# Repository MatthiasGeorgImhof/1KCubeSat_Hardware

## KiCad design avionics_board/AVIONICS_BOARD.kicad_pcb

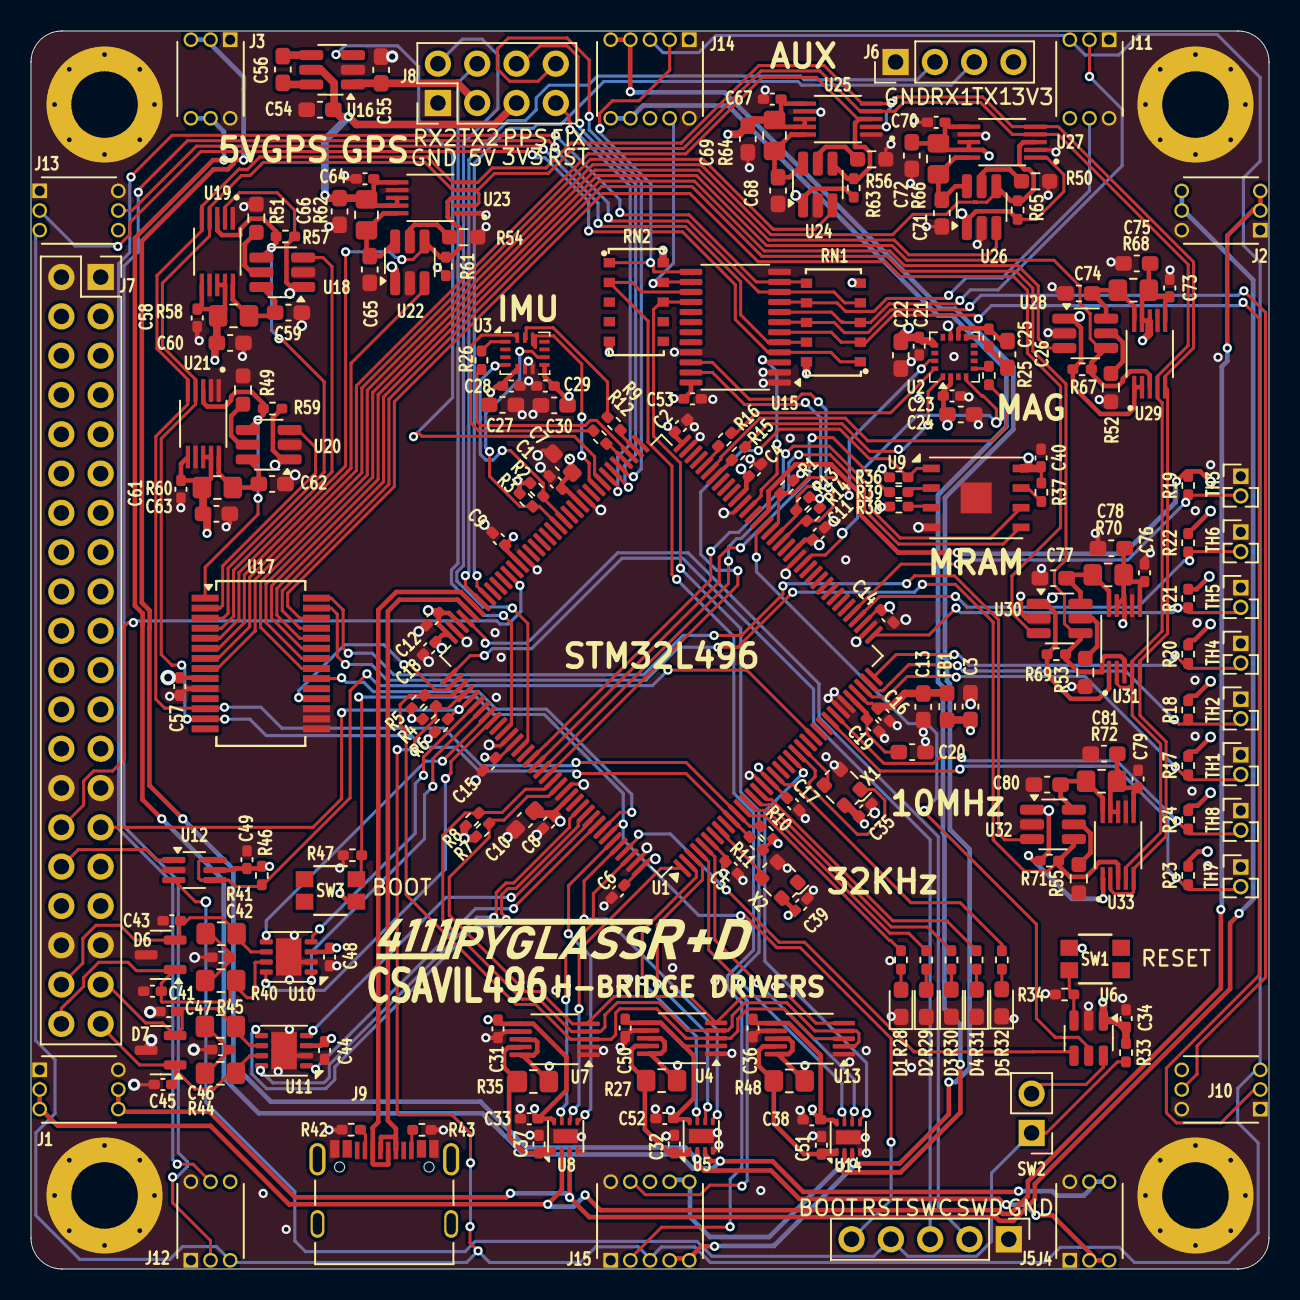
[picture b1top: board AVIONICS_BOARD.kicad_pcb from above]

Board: 4 copper layers, 80.0 x 80.0 mm, 228 parts (0 on the bottom side), 176 nets.

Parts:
C1, C2, C4, C5, C6, C8, C9, C11, C12, C14, C15, C16, C17, C18, C19, C21, C23, C25, C28, C29, C31, C32, C33, C34, C35, C36, C37, C38, C39, C40, C44, C48, C49, C50, C51, C52, C53, C57, C58, C61, C64, C67, C70, C73, C76, C79: 100nF; C_0402_1005Metric_Pad0.74x0.62mm_HandSolder
C3, C7, C10, C13, C20, C22, C24, C26, C27, C30, C54, C55: 10u; C_0603_1608Metric_Pad1.08x0.95mm_HandSolder
C41, C43, C45, C47: 100pF; C_0402_1005Metric_Pad0.74x0.62mm_HandSolder
C42, C46: 4.7nF; C_0402_1005Metric_Pad0.74x0.62mm_HandSolder
C56: 1uF; C_0603_1608Metric_Pad1.08x0.95mm_HandSolder
C59, C60, C62, C63, C65, C66, C68, C69, C71, C72, C74, C75, C77, C78, C80, C81: 10uF; C_0603_1608Metric_Pad1.08x0.95mm_HandSolder
D1: LED_SMD_RED; LED_0603_1608Metric_Pad1.05x0.95mm_HandSolder
D2: LED_SMD_GREEN; LED_0603_1608Metric_Pad1.05x0.95mm_HandSolder
D3, D4, D5: LED_SMD_YELLOW; LED_0603_1608Metric_Pad1.05x0.95mm_HandSolder
D6, D7: NUP2105LT1G; SOT-23
FB1: 120R; L_0603_1608Metric_Pad1.05x0.95mm_HandSolder
H1, H2, H3, H4: MountingHole_Pad; MountingHole_4.3mm_M4_Pad_Via_Custom
J1, J2, J3, J4, J10, J11, J12, J13: Conn_02x03_Odd_Even; HARWIN_M50-3200345
J5: Conn_01x06; PinHeader_1x05_P2.54mm_Vertical
J6: Conn_01x04; PinHeader_1x04_P2.54mm_Vertical
J7: PC104 Conn_02x20_Odd_Even; PinSocket_2x20_P2.54mm_Vertical
J8: Conn_02x04; PinHeader_2x04_P2.54mm_Vertical
J9: 10155435-00011LF; AMPHENOL_10155435-00011LF
J14, J15: Conn_02x05_Odd_Even; HARWIN_M50-3200545
R1, R2, R3, R4, R5, R33, R36, R37, R38, R46, R47, R57, R59, R61, R63, R65, R67, R69, R71: 100K; R_0402_1005Metric_Pad0.72x0.64mm_HandSolder
R6: 330K; R_0402_1005Metric_Pad0.72x0.64mm_HandSolder
R7, R8, R10, R11, R13, R14, R42, R43: 5K1; R_0402_1005Metric_Pad0.72x0.64mm_HandSolder
R9, R12, R15, R16, R25, R26: 22; R_0402_1005Metric_Pad0.72x0.64mm_HandSolder
R17, R18, R19, R20, R21, R22, R23, R24: 47K; R_0402_1005Metric_Pad0.72x0.64mm_HandSolder
R27, R35, R48, R58, R60, R62, R64, R66, R68, R70, R72: 10m; R_0805_2012Metric_Pad1.20x1.40mm_HandSolder
R28, R29, R30, R31, R32: 1K; R_0402_1005Metric_Pad0.72x0.64mm_HandSolder
R34: 8K87; R_0402_1005Metric_Pad0.72x0.64mm_HandSolder
R39: 22R; R_0402_1005Metric_Pad0.72x0.64mm_HandSolder
R40, R41, R44, R45: 60R4; R_0805_2012Metric_Pad1.20x1.40mm_HandSolder
R49, R50, R51, R52, R53, R54, R55, R56: 988R; R_0603_1608Metric_Pad0.98x0.95mm_HandSolder
RN1, RN2: 4K7; C_ARRAY_EXBA_PAN
SW1, SW3: EVP-AA602W; EVP602AA
SW2: SW_DIP_x01; PinHeader_1x02_P2.54mm_Vertical
TH1, TH2, TH3, TH4, TH5, TH6, TH7, TH8: Thermistor_NTC; PinHeader_1x02_P1.27mm_Vertical
U1: STM32L496ZGTx; LQFP-144_20x20mm_P0.5mm
U2: MMC5983MA; LGA-16_3x3mm_P0.5mm
U3: BMI270; Bosch_LGA-14_3x2.5mm_P0.5mm
U4, U7, U13: INA226; VSSOP-10_3x3mm_P0.5mm
U5, U8, U14: DRV8838; WSON-8-1EP_2x2mm_P0.5mm_EP0.9x1.6mm
U6: TPL5010; SOT-23-6
U9: MR25H10; DFN-8-1EP_6x5mm_P1.27mm_EP2x2mm
U10, U11: TCAN3414; VSON-8-1EP_3x3mm_P0.65mm_EP1.65x2.4mm
U12: 74LVC2G07; SOT-363_SC-70-6_Handsoldering
U15: TCA9548APWR; TSSOP-24_4.4x7.8mm_P0.65mm
U16: AP3602AKTR-G1; SOT-23-6_Handsoldering
U17: MCP23017T-E/SS; SSOP-28_5.3x10.2mm_P0.65mm
U18, U20, U22, U24, U26, U28, U30, U32: MIC2009A-1YM6-TR; SOT-23-6_Handsoldering
U19, U21, U23, U25, U27, U29, U31, U33: INA226AIDGSR; SOP50P490X110-10N
X1: 10MHz; Oscillator_SMD_ECS_2520MV-xxx-xx-4Pin_2.5x2.0mm
X2: 32.768KHZ; Oscillator_SMD_ECS_2520MV-xxx-xx-4Pin_2.5x2.0mm

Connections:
/3.3V_ACS_LOGIC: C31.1, C33.1, C36.1, C38.1, C50.1, C52.1, C61.1, C63.1, R60.2, U4.2 (A0), U4.6 (VS), U5.8 (VCC), U7.6 (VS), U8.8 (VCC), U13.6 (VS), U14.8 (VCC), U21.6 (VS), U21.8 (VBUS), U21.9 (IN-)
/3.3V_AUX: C57.1, J7.22, R57.1, R59.1, R61.1, R63.1, R65.1, R67.1, R69.1, R71.1, U17.9 (VDD), U18.1 (VIN), U19.2 (A0), U20.1 (VIN), U22.1 (VIN), U24.1 (VIN), U26.1 (VIN), U27.1 (A1), U28.1 (VIN), U29.1 (A1), U29.2 (A0), U30.1 (VIN), U31.1 (A1), U32.1 (VIN), U33.1 (A1)
/3.3V_CLK: C35.1, C76.1, C78.1, R70.2, U31.6 (VS), U31.8 (VBUS), U31.9 (IN-), X1.4 (VDD)
/3.3V_GPS: C54.1, C64.1, C66.1, J8.5, R62.2, U16.5 (VIN), U23.6 (VS), U23.8 (VBUS), U23.9 (IN-)
/3.3V_GYRO: C27.1, C28.1, C29.1, C30.1, C58.1, C60.1, R58.2, U3.5 (VDDIO), U3.8 (VDD), U19.6 (VS), U19.8 (VBUS), U19.9 (IN-)
/3.3V_MAG: C21.2, C22.1, C23.2, C24.1, C70.1, C72.1, R66.2, U2.2 (VDD), U2.13 (VDDIO), U27.6 (VS), U27.8 (VBUS), U27.9 (IN-)
/3.3V_MRAM: C40.1, C73.1, C75.1, R36.1, R37.1, R38.1, R68.2, U9.8 (VDD), U29.6 (VS), U29.8 (VBUS), U29.9 (IN-)
/3.3V_STM_CORE: C1.1, C2.1, C3.1, C4.1, C5.2, C6.1, C7.2, C8.2, C9.2, C10.2, C11.1, C12.2, C14.1, C15.2, C17.1, C18.2, C34.1, C39.1, C44.1, C48.1, C49.2, FB1.1, J6.4, J7.9, R1.1, R2.1, R3.1, R4.1, R5.1, R6.1, R7.1, R8.1, R10.1, R11.1, R13.1, R14.1, R33.1, R46.1, SW1.1, SW3.1, U1.6 (VBAT), U1.17 (VDD), U1.39 (VDD), U1.52 (VDD), U1.62 (VDD), U1.72 (VDD), U1.84 (VDD), U1.95 (VDDIO2), U1.106 (VDDUSB), U1.108 (VDD), U1.121 (VDD), U1.131 (VDDIO2), U1.144 (VDD), U6.1 (VDD), U10.3 (VCC), U11.3 (VCC), U12.5 (VCC), X2.4 (VCC)
/3.3V_SUN: C53.1, C67.1, C69.1, J10.6, J11.6, J12.6, J13.6, J14.6, J15.6, R64.2, RN1.5, RN1.10, RN2.5, RN2.10, U15.24 (VCC), U25.6 (VS), U25.8 (VBUS), U25.9 (IN-)
/5V_ACS_COIL: J7.5, R27.1, R35.1, R48.1, U4.8 (Vbus), U4.10 (Vin+), U7.8 (Vbus), U7.10 (Vin+), U13.8 (Vbus), U13.10 (Vin+)
/*ATTENTION: J7.29, R6.2, U1.113 (PC12)
/*AVI_RST: J7.32, U12.1 (IN1)
/*EPS_RST: J7.30, U1.97 (PC7)
/ACS/X_N: J1.4, J1.6, J2.4, J2.6, U8.3 (OUT2)
/ACS/X_P: J1.3, J1.5, J2.3, J2.5, U8.2 (OUT1)
/ACS/Y_N: J3.4, J3.6, J4.4, J4.6, U5.3 (OUT2)
/ACS/Y_P: J3.3, J3.5, J4.3, J4.5, U5.2 (OUT1)
/ACS_INT: R5.2, U1.111 (PC10), U4.3 (~Alert), U7.3 (~Alert), U13.3 (~Alert)
/ACS_X_PH: U1.1 (PE2), U8.6 (PH)
/ACS_X_SLEEP: U1.142 (PE1), U8.7 (~SLEEP)
/ACS_Y_PH: U1.3 (PE4), U5.6 (PH)
/ACS_Y_SLEEP: U1.2 (PE3), U5.7 (~SLEEP)
/ACS_Z_PH: U1.5 (PE6), U14.6 (PH)
/ACS_Z_SLEEP: U1.4 (PE5), U14.7 (~SLEEP)
/ADC1_IN3: R23.1, TH7.2, U1.28 (PC2)
/ADC1_IN4: R24.1, TH8.2, U1.29 (PC3)
/ADC1_IN5: R17.1, TH1.2, U1.34 (PA0)
/ADC1_IN6: R18.1, TH2.2, U1.35 (PA1)
/ADC1_IN7: R20.1, TH4.2, U1.36 (PA2)
/ADC1_IN8: R21.1, TH5.2, U1.37 (PA3)
/ADC1_IN9: R22.1, TH6.2, U1.40 (PA4)
/ADC1_IN10: R19.1, TH3.2, U1.41 (PA5)
/CAN1_H: C41.1, D6.1 (K), J7.40, R40.1, U10.7 (CANH)
/CAN1_L: C43.2, D6.2 (K), J7.38, R41.2, U10.6 (CANL)
/CAN2_H: C45.1, D7.1 (K), J7.39, R44.1, U11.7 (CANH)
/CAN2_L: C47.2, D7.2 (K), J7.37, R45.2, U11.6 (CANL)
/GPS_INTERFACE/CAN_POWER6/VOUT: C55.1, J8.3, U16.1 (VOUT)
/GPS_INTERFACE/FIX: J8.8, U1.77 (PD8)
/GPS_INTERFACE/PPS: J8.6, U1.78 (PD9)
/GPS_INTERFACE/SHDN_5V: U1.80 (PD11), U16.3 (*SHDN)
/GPS_RESET: J8.7, U1.79 (PD10)
/GYRO1_INT: R2.2, U1.87 (PG2), U3.4 (INT1)
/GYRO2_INT: R3.2, U1.88 (PG3), U3.9 (INT2)
/GYRO_CS: U1.81 (PD12), U3.12 (CSB)
/I2C1_SCL: R7.2, U1.129 (PG14), U4.5 (SCL), U7.5 (SCL), U13.5 (SCL)
/I2C1_SDA: R8.2, U1.128 (PG13), U4.4 (SDA), U7.4 (SDA), U13.2 (A0), U13.4 (SDA)
/I2C2_SCL: R10.2, U1.11 (PF1), U17.12 (SCL), U19.5 (SCL), U21.5 (SCL), U23.5 (SCL), U25.2 (A0), U25.5 (SCL), U27.5 (SCL), U29.5 (SCL), U31.5 (SCL), U33.2 (A0), U33.5 (SCL)
/I2C2_SDA: R11.2, U1.10 (PF0), U17.13 (SDA), U19.4 (SDA), U21.4 (SDA), U23.2 (A0), U23.4 (SDA), U25.4 (SDA), U27.4 (SDA), U29.4 (SDA), U31.2 (A0), U31.4 (SDA), U33.4 (SDA)
/I2C4_SCL: R14.2, U1.54 (PF14), U15.22 (SCL)
/I2C4_SDA: R13.2, U1.55 (PF15), U15.23 (SDA)
/MAG_CS: U1.50 (PF12), U2.4 (SPI_CS)
/MAG_INT: R1.2, U1.56 (PG0), U2.15 (INT)
/Power_INT_EXTI7: U1.137 (PB7), U17.20 (INTA)
/Power_RST: U1.110 (PA15), U17.18 (*RESET)
/RST_SUN: U1.60 (PE9), U15.3 (~RESET)
/SPI1_MISO: R25.1, U1.67 (PE14)
/SPI1_MOSI: R16.1, U2.16 (SDA/SPI_SDI)
/SPI1_SCK: R15.1, U2.1 (SCL/SPI_SCK)
/SPI2_MISO: R26.2, U1.75 (PB14)
/SPI2_MOSI: R12.2, U3.14 (SDx)
/SPI2_SCK: R9.2, U3.13 (SCx)
/STM32L4/10MHZ_OE: U1.22 (PF10), X1.1 (TRI-STATE)
/STM32L4/BOOT0: J5.5, R47.1, SW3.2, U1.138 (PH3)
/STM32L4/CAN1_RX: U1.114 (PD0), U10.4 (RXD)
/STM32L4/CAN1_SHDN: U1.116 (PD2), U10.5 (SHTD)
/STM32L4/CAN1_STB: U1.117 (PD3), U10.8 (STB)
/STM32L4/CAN1_TX: U1.115 (PD1), U10.1 (TXD)
/STM32L4/CAN2_RX: U1.135 (PB5), U11.4 (RXD)
/STM32L4/CAN2_SHDN: U1.134 (PB4), U11.5 (SHTD)
/STM32L4/CAN2_STB: U1.133 (PB3), U11.8 (STB)
/STM32L4/CAN2_TX: U1.136 (PB6), U11.1 (TXD)
/STM32L4/JTCK_SWCLK: J5.3, U1.109 (PA14)
/STM32L4/JTMS_SWDIO: J5.2, U1.105 (PA13)
/STM32L4/LED_1: R28.1, U1.12 (PF2)
/STM32L4/LED_2: R29.1, U1.13 (PF3)
/STM32L4/LED_3: R30.1, U1.14 (PF4)
/STM32L4/LED_4: R31.1, U1.15 (PF5)
/STM32L4/LED_5: R32.1, U1.18 (PF6)
/STM32L4/MRAM_CS: R36.2, U1.127 (PG12), U9.1 (~CS)
/STM32L4/NRST: R46.2, U1.25 (NRST), U12.4 (OUT2), U12.6 (OUT1)
/STM32L4/RCC_OSC32_IN: U1.8 (PC14), X2.3 (OUT)
/STM32L4/RCC_OSC_IN: U1.23 (PH0), X1.3 (OUTPUT)
/STM32L4/RST: J5.4, R33.2, SW2.1, U12.3 (IN2)
/STM32L4/SPI3_MISO: R39.2, U1.125 (PG10)
/STM32L4/SPI3_MOSI: U1.126 (PG11), U9.5 (SI)
/STM32L4/SPI3_SCK: U1.124 (PG9), U9.6 (SCK)
/STM32L4/USART1_RX: J6.2, U1.102 (PA10)
/STM32L4/USART1_TX: J6.3, U1.101 (PA9)
/STM32L4/USB/DN: J9.A7 (DN1_A), J9.B7 (DN2_B), U1.103 (PA11)
/STM32L4/USB/DP: J9.A6 (DP1_A), J9.B6 (DP2_B), U1.104 (PA12)
/STM32L4/WATCHDOG_DONE: U1.141 (PE0), U6.4 (DONE)
/STM32L4/WATCHDOG_WAKE: U1.57 (PG1), U6.5 (WAKE)
/SUN_INT: J10.5, J11.5, J12.5, J13.5, J14.5, J15.5, R4.2, U1.112 (PC11)
/Solar Sensors/SC0: J13.4, RN1.9, U15.5 (SC0)
/Solar Sensors/SC1: J10.4, RN1.8, U15.7 (SC1)
/Solar Sensors/SC2: J11.4, RN1.7, U15.9 (SC2)
/Solar Sensors/SC3: J12.4, RN1.6, U15.11 (SC3)
/Solar Sensors/SC4: J14.4, RN2.9, U15.14 (SC4)
/Solar Sensors/SC5: J15.4, RN2.8, U15.16 (SC5)
/Solar Sensors/SD0: J13.3, RN1.1, U15.4 (SD0)
/Solar Sensors/SD1: J10.3, RN1.2, U15.6 (SD1)
/Solar Sensors/SD2: J11.3, RN1.3, U15.8 (SD2)
/Solar Sensors/SD3: J12.3, RN1.4, U15.10 (SD3)
/Solar Sensors/SD4: J14.3, RN2.1, U15.13 (SD4)
/Solar Sensors/SD5: J15.3, RN2.2, U15.15 (SD5)
/TEMP_PWR: R17.2, R18.2, R19.2, R20.2, R21.2, R22.2, R23.2, R24.2, U1.58 (PE7)
/TIM15_CH1: U1.21 (PF9), U14.5 (EN)
/TIM16_CH1: U1.139 (PB8), U8.5 (EN)
/TIM17_CH1: U1.140 (PB9), U5.5 (EN)
/USART2_RX: J8.2, U1.122 (PD6)
/USART2_TX: J8.4, U1.119 (PD5)
/Untitled Sheet/ENABLE0: U17.2 (GPB1), U20.3 (ENABLE)
/Untitled Sheet/ENABLE1: U17.4 (GPB3), U18.3 (ENABLE)
/Untitled Sheet/ENABLE2: U17.6 (GPB5), U22.3 (ENABLE)
/Untitled Sheet/ENABLE3: U17.8 (GPB7), U24.3 (ENABLE)
/Untitled Sheet/ENABLE4: U17.22 (GPA1), U26.3 (ENABLE)
/Untitled Sheet/ENABLE5: U17.24 (GPA3), U28.3 (ENABLE)
/Untitled Sheet/ENABLE6: U17.26 (GPA5), U30.3 (ENABLE)
/Untitled Sheet/ENABLE7: U17.28 (GPA7), U32.3 (ENABLE)
/Untitled Sheet/INT0: R59.2, U17.1 (GPB0), U20.4 (*FAULT), U21.3 (ALERT)
/Untitled Sheet/INT1: R57.2, U17.3 (GPB2), U18.4 (*FAULT), U19.3 (ALERT)
/Untitled Sheet/INT2: R61.2, U17.5 (GPB4), U22.4 (*FAULT), U23.3 (ALERT)
/Untitled Sheet/INT3: R63.2, U17.7 (GPB6), U24.4 (*FAULT), U25.3 (ALERT)
/Untitled Sheet/INT4: R65.2, U17.21 (GPA0), U26.4 (*FAULT), U27.3 (ALERT)
/Untitled Sheet/INT5: R67.2, U17.23 (GPA2), U28.4 (*FAULT), U29.3 (ALERT)
/Untitled Sheet/INT6: R69.2, U17.25 (GPA4), U30.4 (*FAULT), U31.3 (ALERT)
/Untitled Sheet/INT7: R71.2, U17.27 (GPA6), U32.4 (*FAULT), U33.3 (ALERT)
/Untitled Sheet/VOUT7: C79.1, C81.1, R72.2, U33.6 (VS), U33.8 (VBUS), U33.9 (IN-)
/Untitled Sheet/sheet601A160D5/ILIMIT+: R53.1, U30.5 (ILIMIT)
/Untitled Sheet/sheet601A160D6/ILIMIT+: R55.1, U32.5 (ILIMIT)
/Untitled Sheet/sheet601A160D7/ILIMIT+: R56.1, U24.5 (ILIMIT)
/Untitled Sheet/sheet601A160D8/ILIMIT+: R54.1, U22.5 (ILIMIT)
/Untitled Sheet/sheet601A160D9/ILIMIT+: R51.1, U18.5 (ILIMIT)
/Untitled Sheet/sheet601A160D10/ILIMIT+: R49.1, U20.5 (ILIMIT)
/Untitled Sheet/sheet601A160D11/ILIMIT+: R50.1, U26.5 (ILIMIT)
/Untitled Sheet/sheet601A160D12/ILIMIT+: R52.1, U28.5 (ILIMIT)
GND: C1.2, C2.2, C3.2, C4.2, C5.1, C6.2, C7.1, C8.1, C9.1, C10.1, C11.2, C12.1, C13.2, C14.2, C15.1, C16.2, C17.2, C18.1, C19.1, C20.1, C21.1, C22.2, C23.1, C24.2, C27.2, C28.2, C29.2, C30.2, C31.2, C32.2, C33.2, C34.2, C35.2, C36.2, C37.2, C38.2, C39.2, C40.2, C41.2, C42.2, C43.1, C44.2, C45.2, C46.2, C47.1, C48.2, C49.1, C50.2, C51.2, C52.2, C53.2, C54.2, C55.2, C57.2, C58.2, C59.2, C60.2, C61.2, C62.2, C63.2, C64.2, C65.2, C66.2, C67.2, C68.2, C69.2, C70.2, C71.2, C72.2, C73.2, C74.2, C75.2, C76.2, C77.2, C78.2, C79.2, C80.2, C81.2, D1.1 (K), D2.1 (K), D3.1 (K), D4.1 (K), D5.1 (K), D6.3 (A), D7.3 (A), H1.1, H2.1, H3.1, H4.1, J1.1, J1.2, J2.1, J2.2, J3.1, J3.2, J4.1, J4.2, J5.1, J6.1, J7.1, J7.2, J7.27, J7.28, J7.35, J7.36, J8.1, J9.A1_B12 (GND), J9.B1_A12 (GND__1), J10.1, J10.2, J11.1, J11.2, J12.1, J12.2, J13.1, J13.2, J14.1, J14.2, J15.1, J15.2, R34.2, R42.1, R43.1, R47.2, R49.2, R50.2, R51.2, R52.2, R53.2, R54.2, R55.2, R56.2, TH1.1, TH2.1, TH3.1, TH4.1, TH5.1, TH6.1, TH7.1, TH8.1, U1.16 (VSS), U1.30 (VSSA), U1.31 (VREF-), U1.38 (VSS), U1.51 (VSS), U1.61 (VSS), U1.71 (VSS), U1.83 (VSS), U1.94 (VSS), U1.107 (VSS), U1.120 (VSS), U1.130 (VSS), U1.143 (VSS), U2.11 (VSS), U3.6 (GNDIO), U3.7 (GND), U4.1 (A1), U4.7 (GND), U5.4 (GND), U5.9 (GND), U6.2 (GND), U7.1 (A1), U7.2 (A0), U7.7 (GND), U8.4 (GND), U8.9 (GND), U9.4 (VSS), U9.9 (PAD), U10.2 (GND), U10.9 (GND), U11.2 (GND), U11.9 (GND), U12.2 (GND), U13.1 (A1), U13.7 (GND), U14.4 (GND), U14.9 (GND), U15.1 (A0), U15.2 (A1), U15.12 (GND), U15.21 (A2), U16.2 (GND), U17.10 (VSS), U17.15 (A0), U17.16 (A1), U17.17 (A2), U18.2 (GND), U19.1 (A1), U19.7 (GND), U20.2 (GND), U21.1 (A1), U21.2 (A0), U21.7 (GND), U22.2 (GND), U23.1 (A1), U23.7 (GND), U24.2 (GND), U25.1 (A1), U25.7 (GND), U26.2 (GND), U27.2 (A0), U27.7 (GND), U28.2 (GND), U29.7 (GND), U30.2 (GND), U31.7 (GND), U32.2 (GND), U33.7 (GND), X1.2 (GND), X2.2 (GND)
unnamed: C25.1, C26.1, U2.9 (VSS)
unnamed: C42.1, R40.2, R41.1
unnamed: C46.1, R44.2, R45.1
unnamed: D1.2 (A), R28.2
unnamed: D2.2 (A), R29.2
unnamed: D3.2 (A), R30.2
unnamed: D4.2 (A), R31.2
unnamed: D5.2 (A), R32.2
unnamed: J9.A5 (CC1_A), R42.2
unnamed: J9.B5 (CC2_B), R43.2
unnamed: R9.1, U1.74 (PB13)
unnamed: R12.1, U1.76 (PB15)
unnamed: R15.2, U1.66 (PE13)
unnamed: R16.2, U1.68 (PE15)
unnamed: C13.1, C16.1, FB1.2, U1.33 (VDDA)
unnamed: C19.2, C20.2, U1.32 (VREF+)
unnamed: C25.2, C26.2, U2.10 (CAP)
unnamed: R25.2, U2.5 (SPI_SDO)
unnamed: R26.1, U3.1 (SDO)
unnamed: C32.1, R27.2, U4.9 (Vin-), U5.1 (VM)
unnamed: R34.1, SW1.2, U6.3 (DELAY/M_RST)
unnamed: SW2.2, U6.6 (~RST)
unnamed: C37.1, R35.2, U7.9 (Vin-), U8.1 (VM)
unnamed: R39.1, U9.2 (SO)
unnamed: R37.2, U9.7 (~HOLD)
unnamed: R38.2, U9.3 (~WP)
unnamed: C51.1, R48.2, U13.9 (Vin-), U14.1 (VM)
unnamed: C56.2, U16.6 (C+)
unnamed: C56.1, U16.4 (C-)
unnamed: C59.1, R58.1, U18.6 (VOUT), U19.10 (IN+)
unnamed: C62.1, R60.1, U20.6 (VOUT), U21.10 (IN+)
unnamed: C65.1, R62.1, U22.6 (VOUT), U23.10 (IN+)
unnamed: C68.1, R64.1, U24.6 (VOUT), U25.10 (IN+)
unnamed: C71.1, R66.1, U26.6 (VOUT), U27.10 (IN+)
unnamed: C74.1, R68.1, U28.6 (VOUT), U29.10 (IN+)
unnamed: C77.1, R70.1, U30.6 (VOUT), U31.10 (IN+)
unnamed: C80.1, R72.1, U32.6 (VOUT), U33.10 (IN+)
Z_N: J14.7, J14.9, J15.7, J15.9, U14.3 (OUT2)
Z_P: J14.8, J14.10, J15.8, J15.10, U14.2 (OUT1)

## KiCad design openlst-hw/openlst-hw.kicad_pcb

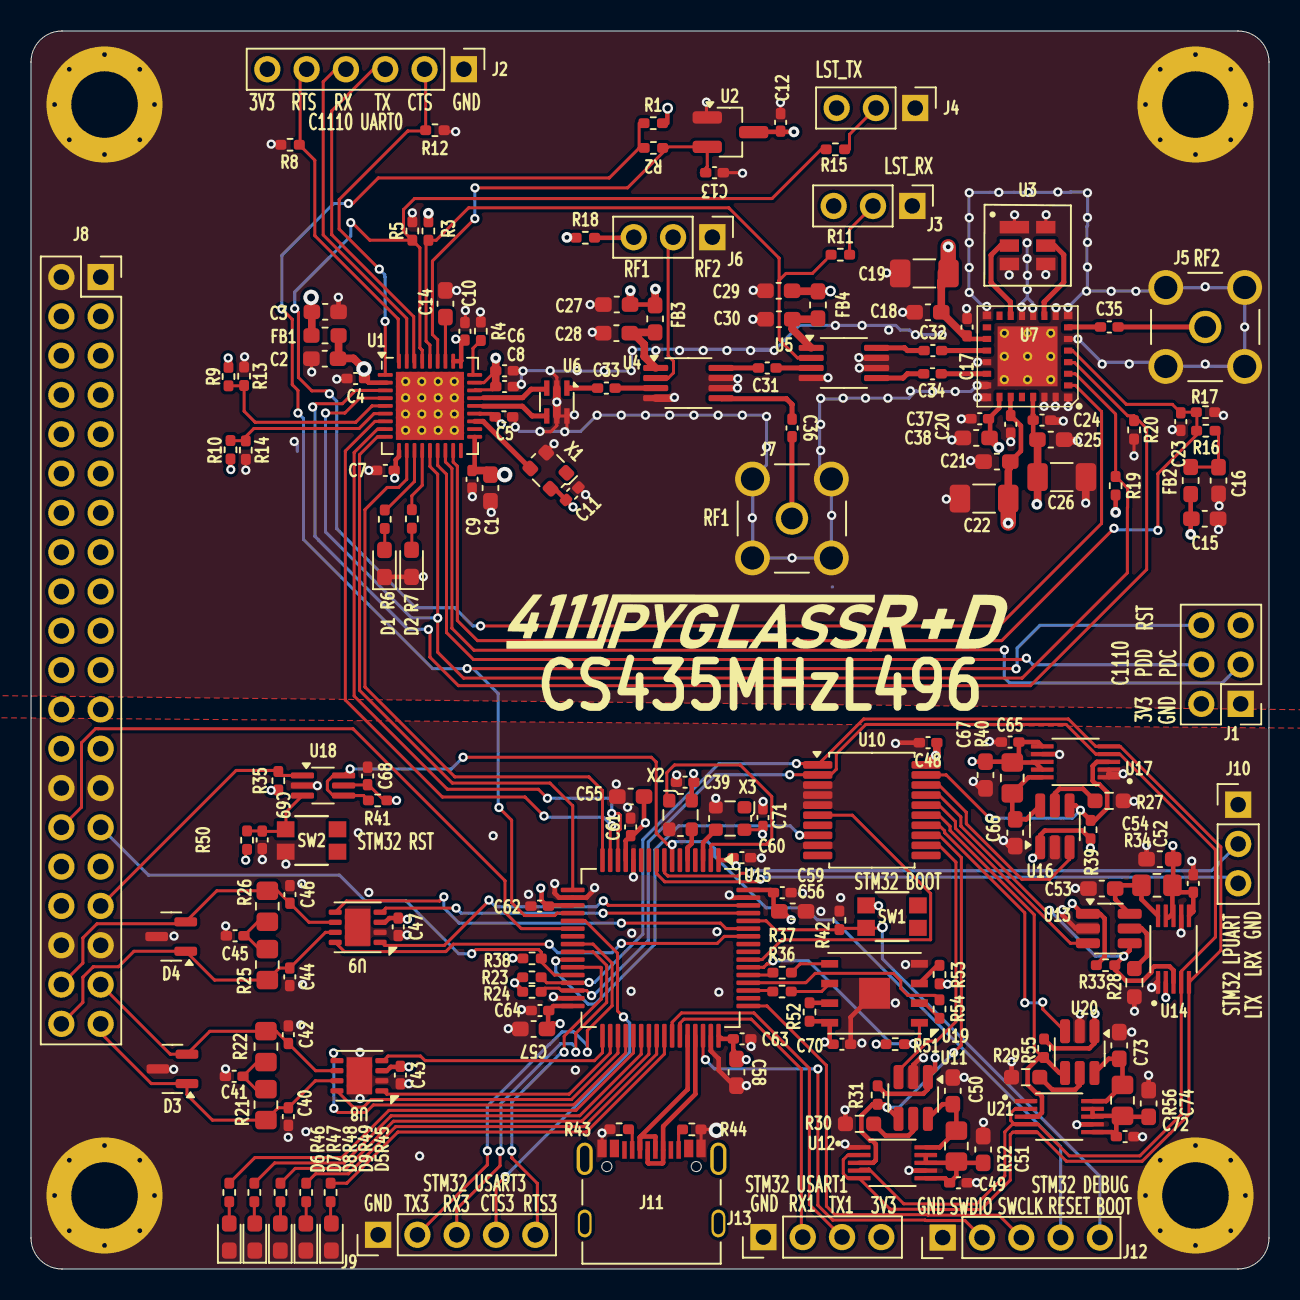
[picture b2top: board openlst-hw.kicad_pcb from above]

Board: 4 copper layers, 80.0 x 80.0 mm, 186 parts (0 on the bottom side), 134 nets.

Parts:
C1, C18, C21, C25, C38, C50, C51, C53, C54, C55, C56, C57, C58, C66, C67, C73, C74: 10uF; C_0603_1608Metric_Pad1.08x0.95mm_HandSolder
C2, C3, C14, C15, C16, C27, C28, C29, C30: 1uF; C_0603_1608Metric_Pad1.08x0.95mm_HandSolder
C4, C5, C6, C7, C8, C9, C10, C11, C12, C13, C17, C20, C23, C24, C37, C39, C43, C47, C48, C49, C52, C59, C60, C61, C62, C63, C64, C65, C68, C69, C70, C71, C72: 100nF; C_0402_1005Metric_Pad0.74x0.62mm_HandSolder
C19, C22, C26: 47uF; C_1206_3216Metric_Pad1.33x1.80mm_HandSolder
C31, C32, C33, C34, C35, C36: 220pF; C_0402_1005Metric_Pad0.74x0.62mm_HandSolder
C40, C42, C44, C46: 100pF; C_0402_1005Metric_Pad0.74x0.62mm_HandSolder
C41, C45: 4.7nF; C_0402_1005Metric_Pad0.74x0.62mm_HandSolder
D1, D2: ORANGE; LED_0603_1608Metric_Pad1.05x0.95mm_HandSolder
D3, D4: NUP2105LT1G; SOT-23
D5: LED_SMD_RED; LED_0603_1608Metric_Pad1.05x0.95mm_HandSolder
D6: LED_SMD_GREEN; LED_0603_1608Metric_Pad1.05x0.95mm_HandSolder
D7, D8, D9: LED_SMD_YELLOW; LED_0603_1608Metric_Pad1.05x0.95mm_HandSolder
FB1, FB2, FB3, FB4: 1K; L_0603_1608Metric_Pad1.05x0.95mm_HandSolder
H1, H2, H3, H4: MountingHole_Pad; MountingHole_4.3mm_M4_Pad_Via_Custom
J1: Conn_02x03_Pin; PinHeader_2x03_P2.54mm_Vertical
J2: Conn_01x06_Pin; PinHeader_1x06_P2.54mm_Vertical
J3, J4, J6, J10: Conn_01x03_Pin; PinHeader_1x03_P2.54mm_Vertical
J5, J7: SMA Jack; LINX_CONSMA001-G
J8: PC104 Conn_02x20_Odd_Even; PinSocket_2x20_P2.54mm_Vertical
J9: Conn_01x05_Pin; PinHeader_1x05_P2.54mm_Vertical
J11: 10155435-00011LF; AMPHENOL_10155435-00011LF
J12: Conn_01x06; PinHeader_1x05_P2.54mm_Vertical
J13: Conn_01x04; PinHeader_1x04_P2.54mm_Vertical
R1, R13, R14: 47K; R_0402_1005Metric_Pad0.72x0.64mm_HandSolder
R2, R6, R7, R19, R20, R45, R46, R47, R48, R49: 1K; R_0402_1005Metric_Pad0.72x0.64mm_HandSolder
R3, R5: 10K; R_0402_1005Metric_Pad0.72x0.64mm_HandSolder
R4: 56K; R_0402_1005Metric_Pad0.72x0.64mm_HandSolder
R8, R12, R31, R33, R35, R39, R41, R42, R50, R51, R52, R53, R55: 100K; R_0402_1005Metric_Pad0.72x0.64mm_HandSolder
R9, R10, R18: 20K; R_0402_1005Metric_Pad0.72x0.64mm_HandSolder
R11, R15: 22; R_0402_1005Metric_Pad0.72x0.64mm_HandSolder
R16: 3.09K; R_0402_1005Metric_Pad0.72x0.64mm_HandSolder
R17: 6.65K; R_0402_1005Metric_Pad0.72x0.64mm_HandSolder
R21, R22, R25, R26: 60R4; R_0805_2012Metric_Pad1.20x1.40mm_HandSolder
R23, R24, R43, R44: 5K1; R_0402_1005Metric_Pad0.72x0.64mm_HandSolder
R27, R28, R29, R30: 988R; R_0603_1608Metric_Pad0.98x0.95mm_HandSolder
R32, R34, R40, R56: 10m; R_0805_2012Metric_Pad1.20x1.40mm_HandSolder
R36, R37, R54: 22R; R_0402_1005Metric_Pad0.72x0.64mm_HandSolder
R38: 300K; R_0402_1005Metric_Pad0.72x0.64mm_HandSolder
SW1, SW2: EVP-AA602W; EVP602AA
U1: CC1110; Texas_RHH0036C_VQFN-36-1EP_6x6mm_P0.5mm_EP4.4x4.4mm_Thermal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
U2: MIC803; SOT-23_Handsoldering
U3: SF2446E
U4, U5: PE4250MLI; MSOP-8_3x3mm_P0.65mm
U6: 0433BM15A0001; Balun_Johanson_0896BM15A0001
U7: RFFM6406
U8, U9: TCAN3414; VSON-8-1EP_3x3mm_P0.65mm_EP1.65x2.4mm
U10: MCP23008T-E/SS; SSOP-20_5.3x7.2mm_P0.65mm
U11, U13, U16, U20: MIC2009A-1YM6-TR; SOT-23-6_Handsoldering
U12, U14, U17, U21: INA226AIDGSR; SOP50P490X110-10N
U15: STM32L496RGTx; LQFP-64_10x10mm_P0.5mm
U18: 74LVC2G07; SOT-363_SC-70-6_Handsoldering
U19: MR25H10; DFN-8-1EP_6x5mm_P1.27mm_EP2x2mm
X1: 27MHz; Oscillator_SMD_ECS_2520MV-xxx-xx-4Pin_2.5x2.0mm
X2: 10MHz; Oscillator_SMD_ECS_2520MV-xxx-xx-4Pin_2.5x2.0mm
X3: 32.768KHZ; Oscillator_SMD_ECS_2520MV-xxx-xx-4Pin_2.5x2.0mm

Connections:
/3V3_COMM: C3.1, C11.1, C12.2, C15.1, C27.1, C29.1, C37.1, C38.1, C65.1, C67.1, FB1.1, FB2.2, FB3.2, FB4.2, J1.2, J2.6, J3.3, J4.3, R1.2, R3.2, R9.2, R18.1, R19.2, R40.2, U2.3 (VCC), U7.23 (VDD), U17.6 (VS), U17.8 (VBUS), U17.9 (IN-), X1.4 (Vcc)
/CAN Bridge/3V3_MRAM: C52.1, C54.1, C70.1, R34.2, R51.1, R52.1, R53.1, U14.6 (VS), U14.8 (VBUS), U14.9 (IN-), U19.8 (VDD)
/CAN Bridge/ATTENTION: J8.29, R38.2, U15.28 (PB2)
/CAN Bridge/CAN1_H: C44.1, D4.1 (K), J8.40, R25.1, U9.7 (CANH)
/CAN Bridge/CAN1_L: C46.2, D4.2 (K), J8.38, R26.2, U9.6 (CANL)
/CAN Bridge/CAN2_H: C40.1, D3.1 (K), J8.39, R21.1, U8.7 (CANH)
/CAN Bridge/CAN2_L: C42.2, D3.2 (K), J8.37, R22.2, U8.6 (CANL)
/CAN Bridge/CAN Transceiver1/CAN_RX: U9.4 (RXD), U15.61 (PB8)
/CAN Bridge/CAN Transceiver1/CAN_TX: U9.1 (TXD), U15.62 (PB9)
/CAN Bridge/CAN Transceiver1/SHDN: U9.5 (SHTD), U15.59 (PB7)
/CAN Bridge/CAN Transceiver1/STB: U9.8 (STB), U15.58 (PB6)
/CAN Bridge/CAN Transceiver2/CAN_RX: U8.4 (RXD), U15.33 (PB12)
/CAN Bridge/CAN Transceiver2/CAN_TX: U8.1 (TXD), U15.34 (PB13)
/CAN Bridge/CAN Transceiver2/SHDN: U8.5 (SHTD), U15.36 (PB15)
/CAN Bridge/CAN Transceiver2/STB: U8.8 (STB), U15.35 (PB14)
/CAN Bridge/EPS_RST: J8.30, U15.22 (PA6)
/CAN Bridge/I2C2_SCL: R23.2, U10.1 (SCL), U12.2 (A0), U12.5 (SCL), U14.5 (SCL), U15.29 (PB10), U17.5 (SCL), U21.5 (SCL)
/CAN Bridge/I2C2_SDA: R24.2, U10.2 (SDA), U12.4 (SDA), U14.4 (SDA), U15.30 (PB11), U17.4 (SDA), U21.2 (A0), U21.4 (SDA)
/CAN Bridge/MRAM/SPI_CLK: R36.1, U19.6 (SCK)
/CAN Bridge/MRAM/SPI_CS: R51.2, U15.54 (PD2), U19.1 (~CS)
/CAN Bridge/MRAM/SPI_MISO: R54.2, U15.52 (PC11)
/CAN Bridge/MRAM/SPI_MOSI: R37.1, U19.5 (SI)
/CAN Bridge/PMIC/BOOT: J12.5, R42.1, SW1.2, U15.60 (PH3_BOOT0)
/CAN Bridge/PMIC/EXTR_RST: J8.33, R35.2, U18.1 (IN1)
/CAN Bridge/PMIC/HSE_EN: U15.2 (PC13), X2.1 (TRI-STATE)
/CAN Bridge/PMIC/HSE_IN: U15.5 (PH0), X2.3 (OUTPUT)
/CAN Bridge/PMIC/LED1: R45.1, U15.37 (PC6)
/CAN Bridge/PMIC/LED2: R46.1, U15.38 (PC7)
/CAN Bridge/PMIC/LED3: R47.1, U15.39 (PC8)
/CAN Bridge/PMIC/LED4: R48.1, U15.40 (PC9)
/CAN Bridge/PMIC/LED5: R49.1, U15.41 (PA8)
/CAN Bridge/PMIC/LPUART_RX: J10.2, U15.8 (PC0)
/CAN Bridge/PMIC/LPUART_TX: J10.3, U15.9 (PC1)
/CAN Bridge/PMIC/OSC32_IN: U15.3 (PC14), X3.3 (OUT)
/CAN Bridge/PMIC/RESET: J12.4, R41.2, U15.7 (NRST), U18.4 (OUT2), U18.6 (OUT1)
/CAN Bridge/PMIC/RESET/RESET: C69.1, R50.2, SW2.3, U18.3 (IN2)
/CAN Bridge/PMIC/SYS_JTMS_SWCLK: J12.3, U15.49 (PA14)
/CAN Bridge/PMIC/SYS_JTMS_SWDIO: J12.2, U15.46 (PA13)
/CAN Bridge/PMIC/USART1_RX: J13.2, U15.43 (PA10)
/CAN Bridge/PMIC/USART1_TX: J13.3, U15.42 (PA9)
/CAN Bridge/PMIC/USART3_CTS: J9.4, U15.21 (PA5)
/CAN Bridge/PMIC/USART3_RTS: J9.5, U15.27 (PB1)
/CAN Bridge/PMIC/USART3_RX: J9.3, U15.25 (PC5)
/CAN Bridge/PMIC/USART3_TX: J9.2, U15.24 (PC4)
/CAN Bridge/PMIC/USB/DN: J11.A7 (DN1_A), J11.B7 (DN2_B), U15.44 (PA11)
/CAN Bridge/PMIC/USB/DP: J11.A6 (DP1_A), J11.B6 (DP2_B), U15.45 (PA12)
/CAN Bridge/Power Switch/ENABLE0: U10.18 (GP6), U16.3 (ENABLE)
/CAN Bridge/Power Switch/ENABLE1: U10.16 (GP4), U13.3 (ENABLE)
/CAN Bridge/Power Switch/ENABLE2: U10.14 (GP2), U20.3 (ENABLE)
/CAN Bridge/Power Switch/ENABLE3: U10.12 (GP0), U11.3 (ENABLE)
/CAN Bridge/Power Switch/INT0: R39.2, U10.19 (GP7), U16.4 (*FAULT), U17.3 (ALERT)
/CAN Bridge/Power Switch/INT1: R33.2, U10.17 (GP5), U13.4 (*FAULT), U14.3 (ALERT)
/CAN Bridge/Power Switch/INT2: R55.2, U10.15 (GP3), U20.4 (*FAULT), U21.3 (ALERT)
/CAN Bridge/Power Switch/INT3: R31.2, U10.13 (GP1), U11.4 (*FAULT), U12.3 (ALERT)
/CAN Bridge/Power Switch/VOUT2: C72.1, C74.1, R56.2, U21.6 (VS), U21.8 (VBUS), U21.9 (IN-)
/CAN Bridge/Power Switch/VOUT3: C49.1, C51.1, R32.2, U12.6 (VS), U12.8 (VBUS), U12.9 (IN-)
/CAN Bridge/Power Switch/sheet601A160D1/ILIMIT+: R27.1, U16.5 (ILIMIT)
/CAN Bridge/Power Switch/sheet601A160D2/ILIMIT+: R28.1, U13.5 (ILIMIT)
/CAN Bridge/Power Switch/sheet601A160D3/ILIMIT+: R29.1, U20.5 (ILIMIT)
/CAN Bridge/Power Switch/sheet601A160D4/ILIMIT+: R30.1, U11.5 (ILIMIT)
/CAN Bridge/Power_INT: U10.8 (INT), U15.26 (PB0)
/CAN Bridge/Power_RST: U10.6 (*RESET), U15.55 (PB3)
/CAN Bridge/UART_CTS: U1.8 (P0_3), U15.14 (PA0)
/CAN Bridge/UART_RTS: U1.7 (P0_2), U15.15 (PA1)
/CAN Bridge/UART_RX: U1.9 (P0_4), U15.17 (PA3)
/CAN Bridge/UART_TX: U1.11 (P0_5), U15.16 (PA2)
/GND: C1.2, C2.2, C3.2, C4.2, C5.2, C6.2, C7.2, C8.2, C9.2, C10.2, C11.2, C12.1, C13.1, C14.2, C15.2, C16.2, C17.2, C18.2, C19.2, C20.2, C21.2, C22.2, C23.2, C24.2, C25.2, C26.2, C27.2, C28.2, C29.2, C30.2, C37.2, C38.2, C39.2, C40.2, C41.2, C42.1, C43.2, C44.2, C45.2, C46.1, C47.2, C48.2, C49.2, C50.2, C51.2, C52.2, C53.2, C54.2, C55.2, C56.2, C57.2, C58.2, C59.2, C60.2, C61.2, C62.2, C63.2, C64.2, C65.2, C66.2, C67.2, C68.1, C69.2, C70.2, C71.2, C72.2, C73.2, C74.2, D1.1 (K), D2.1 (K), D3.3 (A), D4.3 (A), D5.1 (K), D6.1 (K), D7.1 (K), D8.1 (K), D9.1 (K), H1.1, H2.1, H3.1, H4.1, J1.1, J2.1, J3.1, J4.1, J5.2 (Ext), J6.1, J7.2 (Ext), J8.1, J8.2, J8.27, J8.28, J8.35, J8.36, J9.1, J10.1, J11.A1_B12 (GND), J11.B1_A12 (GND__1), J12.1, J13.1, R4.1, R5.1, R8.1, R12.1, R13.1, R14.1, R17.2, R20.1, R27.2, R28.2, R29.2, R30.2, R42.2, R43.1, R44.1, SW2.4, U1.37 (GND_PAD), U2.1 (GND), U3.1 (GND), U3.3 (GND), U3.4 (GND), U3.6 (GND), U4.4 (GND), U4.6 (GND), U4.7 (GND), U5.4 (GND), U5.6 (GND), U5.7 (GND), U6.2 (GND), U6.5 (GND), U6.6 (GND), U7.1 (GND), U7.6 (GND), U7.8 (GND), U7.9 (GND), U7.11 (GND), U7.12 (GND), U7.15 (GND), U7.19 (GND), U7.21 (GND), U7.22 (GND), U7.27 (GND), U7.28 (GND), U7.29 (PAD), U8.2 (GND), U8.9 (GND), U9.2 (GND), U9.9 (GND), U10.3 (A2), U10.4 (A1), U10.5 (A0), U10.9 (VSS), U11.2 (GND), U12.1 (A1), U12.7 (GND), U13.2 (GND), U14.1 (A1), U14.7 (GND), U15.12 (VSSA), U15.18 (VSS), U15.31 (VSS), U15.47 (VSS), U15.63 (VSS), U16.2 (GND), U17.1 (A1), U17.2 (A0), U17.7 (GND), U18.2 (GND), U19.4 (VSS), U19.9 (PAD), U20.2 (GND), U21.1 (A1), U21.7 (GND), X1.2 (GND), X2.2 (GND), X3.2 (GND)
/INTERBOARD_CONNECTOR2/3V3_17_RF1_BRIDGE: C39.1, C43.1, C47.1, C55.1, C56.1, C57.1, C58.1, C59.1, C60.1, C61.1, C62.1, C63.1, C64.1, C68.2, C71.1, J8.23, J13.4, R23.1, R24.1, R35.1, R38.1, R41.1, R50.1, SW1.1, U8.3 (VCC), U9.3 (VCC), U15.1 (VBAT), U15.13 (VDDA), U15.19 (VDD), U15.32 (VDD), U15.48 (VDDUSB), U15.64 (VDD), U18.5 (VCC), X2.4 (VDD), X3.4 (VCC)
/INTERBOARD_CONNECTOR2/3V3_18_RF1_COMM: C48.1, J8.24, R31.1, R33.1, R39.1, R55.1, U10.20 (VDD), U11.1 (VIN), U13.1 (VIN), U14.2 (A0), U16.1 (VIN), U20.1 (VIN)
/INTERBOARD_CONNECTOR2/BATT_1_COMM1_VRF: C17.1, C18.1, C19.1, C20.1, C21.1, C22.1, C24.1, C25.1, C26.1, J8.3, R10.2, U7.17 (VCC_RX), U7.24 (VCC_TX1), U7.26 (VCC_TX2)
/MCU/+3V3_C1110: C1.1, C2.1, C4.1, C5.1, C6.1, C7.1, C8.1, C9.1, C10.1, FB1.2, U1.2 (DVDD), U1.10 (DVDD), U1.19 (AVDD), U1.22 (AVDD), U1.25 (AVDD), U1.26 (AVDD), U1.28 (GUARD), U1.29 (AVDD_DREG)
/MCU/AN0: R9.1, R13.2, U1.5 (P0_0)
/MCU/AN1: R10.1, R14.2, U1.6 (P0_1)
/MCU/LST_RX_MODE: R3.1, R11.1, U1.32 (P1_7), U5.2 (V1)
/MCU/LST_TX_MODE: R5.2, R15.1, U1.33 (P1_6), U7.2 (TR)
/MCU/PA_VAPC: C23.1, R16.2, R17.1, U1.17 (P2_3/XOSC32-1), U7.5 (VAPC)
/MCU/RF_BYP: R20.2, U1.3 (P1_1), U7.4 (BYP)
/MCU/RF_EN: R19.1, U1.4 (P1_0), U1.14 (P2_0), U7.3 (EN)
/MCU/RF_N: U1.24 (RF_N), U6.3
/MCU/RF_P: U1.23 (RF_P), U6.4
/MCU/UART0_CTS: J2.2, R12.2, U1.1 (P1_2)
/MCU/UART0_RTS: J2.5, R8.2, U1.36 (P1_3)
/MCU/UART0_RX: J2.4, U1.35 (P1_4)
/MCU/UART0_TX: J2.3, U1.34 (P1_5)
LED1: R6.2, U1.12 (P0_6)
LED2: R7.2, U1.13 (P0_7)
LST_RESET: J1.6, R1.1, R2.2, U15.20 (PA4)
unnamed: C16.1, FB2.1, R16.1
unnamed: C33.1, U6.1
unnamed: C41.1, R21.2, R22.1
unnamed: C45.1, R25.2, R26.1
unnamed: D1.2 (A), R6.1
unnamed: D2.2 (A), R7.1
unnamed: D5.2 (A), R45.2
unnamed: D6.2 (A), R46.2
unnamed: D7.2 (A), R47.2
unnamed: D8.2 (A), R48.2
unnamed: D9.2 (A), R49.2
unnamed: J3.2, R11.2
unnamed: J4.2, R15.2
unnamed: C35.2, J5.1 (In)
unnamed: J6.2, U4.2 (V1)
unnamed: J6.3, R18.2
unnamed: C36.2, J7.1 (In)
unnamed: J11.A5 (CC1_A), R43.2
unnamed: J11.B5 (CC2_B), R44.2
unnamed: C14.1, U1.30 (DCOUPL)
unnamed: R4.2, U1.27 (RBIAS)
unnamed: C13.2, R2.1, U1.31 (RESET_N), U2.2 (RESET)
unnamed: U1.21 (XOSC-1), X1.3 (OUT)
unnamed: C36.1, U4.5 (RF1)
unnamed: C31.1, U4.8 (RF2)
unnamed: C33.2, U4.3 (RFC)
unnamed: C28.1, FB3.1, U4.1 (V2)
unnamed: C34.1, U5.5 (RF1)
unnamed: C32.1, U5.8 (RF2)
unnamed: C31.2, U5.3 (RFC)
unnamed: C30.1, FB4.1, U5.1 (V2)
unnamed: C35.1, U7.7 (ANT)
unnamed: C32.2, U7.18 (RX)
unnamed: U3.5 (RF), U7.10 (SAW1)
unnamed: U3.2 (RF), U7.13 (SAW2)
unnamed: C34.2, U7.20 (TX)
unnamed: C50.1, R32.1, U11.6 (VOUT), U12.10 (IN+)
unnamed: C53.1, R34.1, U13.6 (VOUT), U14.10 (IN+)
unnamed: R36.2, U15.51 (PC10)
unnamed: R37.2, U15.53 (PC12)
unnamed: C66.1, R40.1, U16.6 (VOUT), U17.10 (IN+)
unnamed: R54.1, U19.2 (SO)
unnamed: R52.2, U19.7 (~HOLD)
unnamed: R53.2, U19.3 (~WP)
unnamed: C73.1, R56.1, U20.6 (VOUT), U21.10 (IN+)
PROG_DC: J1.3, U1.16 (P2_2)
PROG_DD: J1.4, U1.15 (P2_1)
